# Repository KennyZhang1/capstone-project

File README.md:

# Introduction
This repo contains the source code for our ECE Capstone Project: Robotic Vehicle Glove Controller

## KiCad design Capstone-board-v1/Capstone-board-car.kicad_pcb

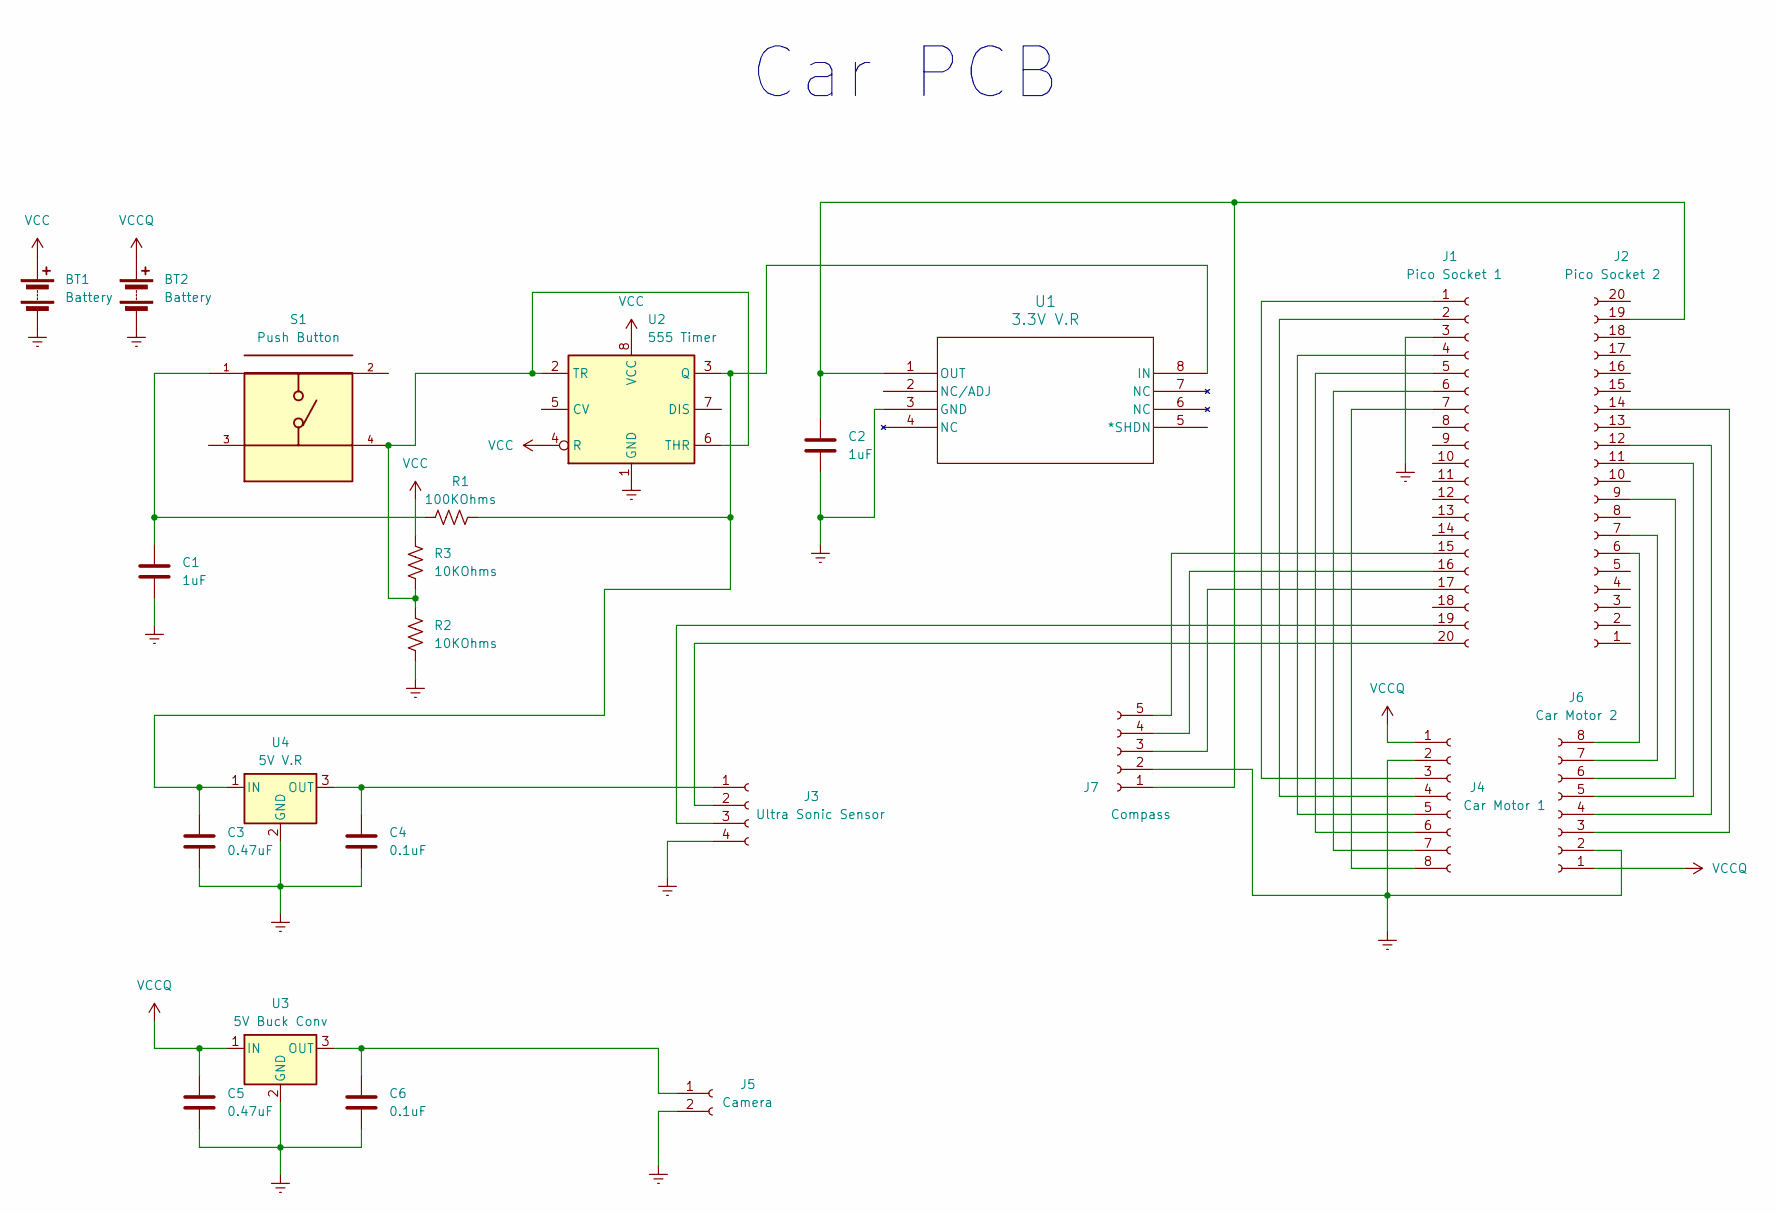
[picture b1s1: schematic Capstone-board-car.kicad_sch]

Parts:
BT1: Battery; Hirose_DF11-6DP-2DSA_2x03_P2.00mm_Vertical
BT2: Battery; PinHeader_1x02_P2.54mm_Vertical
C1, C2: 1uF; CP_Radial_Tantal_D4.5mm_P5.00mm
C3, C5: 0.47uF; CP_Radial_Tantal_D4.5mm_P5.00mm
C4, C6: 0.1uF; CP_Radial_Tantal_D4.5mm_P5.00mm
J1: Pico Socket 1; PinSocket_1x20_P2.54mm_Vertical
J2: Pico Socket 2; PinSocket_1x20_P2.54mm_Vertical
J3: Ultra Sonic Sensor; PinHeader_1x04_P2.54mm_Vertical
J4: Car Motor 1; PinHeader_1x08_P2.54mm_Vertical
J5: Camera; PinHeader_1x02_P2.54mm_Vertical
J6: Car Motor 2; PinSocket_1x08_P2.54mm_Vertical
J7: Compass; PinSocket_1x05_P2.54mm_Vertical
R1: 100KOhms; R_Axial_DIN0204_L3.6mm_D1.6mm_P5.08mm_Horizontal
R2, R3: 10KOhms; R_Axial_DIN0204_L3.6mm_D1.6mm_P5.08mm_Horizontal
S1: Push Button; SW_TS02-66-60-BK-160-LCR-D; PARTREV 1.0
U1: 3.3V V.R; DIP-8_W7.62mm_Socket
U2: 555 Timer; DIP-8_W7.62mm_Socket
U3: 5V Buck Conv; TO255P1040X460X1968-3
U4: 5V V.R; TO255P1040X460X1968-3

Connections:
Earth: BT1.2 (-), BT2.2 (-), C1.2, C2.2, C3.2, C4.2, C5.2, C6.2, J1.3, J3.4, J4.2, J5.2, J6.2, J7.2, R2.1, U1.3 (GND), U2.1 (GND), U3.2 (GND), U4.2 (GND)
unnamed: C1.1, R1.1, S1.1
unnamed: J1.1, J4.3
unnamed: J1.2, J4.4
unnamed: J1.4, J4.5
unnamed: J1.5, J4.6
unnamed: J1.6, J4.7
unnamed: J1.7, J4.8
unnamed: J1.15, J7.5
unnamed: J1.16, J7.4
unnamed: J1.17, J7.3
unnamed: J1.19, J3.3
unnamed: J1.20, J3.2
unnamed: J2.6, J6.8
unnamed: J2.7, J6.7
unnamed: J2.9, J6.6
unnamed: J2.11, J6.5
unnamed: J2.12, J6.4
unnamed: J2.14, J6.3
unnamed: C2.1, J2.19, J7.1, U1.1 (OUT)
unnamed: C4.1, J3.1, U4.3 (OUT)
unnamed: C6.1, J5.1, U3.3 (OUT)
unnamed: C3.1, R1.2, U1.8 (IN), U2.3 (Q), U4.1 (IN)
unnamed: R2.2, R3.1, S1.4, U2.2 (TR), U2.6 (THR)
VCC: BT1.1 (+), R3.2, U2.4 (R), U2.8 (VCC)
VCCQ: BT2.1 (+), C5.1, J4.1, J6.1, U3.1 (IN)

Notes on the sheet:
Car PCB

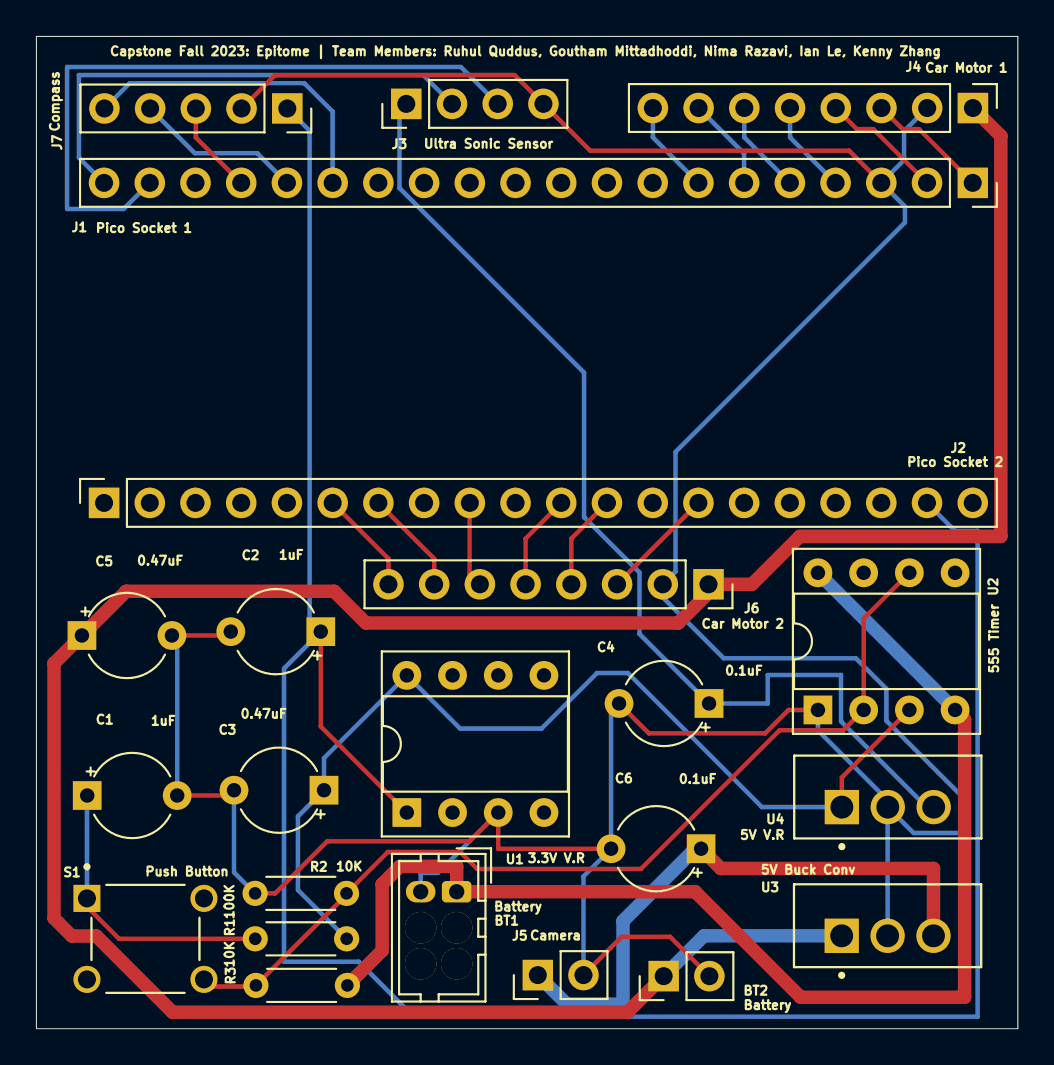
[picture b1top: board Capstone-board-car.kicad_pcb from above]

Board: 2 copper layers, 54.5 x 55.1 mm, 23 parts (0 on the bottom side), 26 nets.

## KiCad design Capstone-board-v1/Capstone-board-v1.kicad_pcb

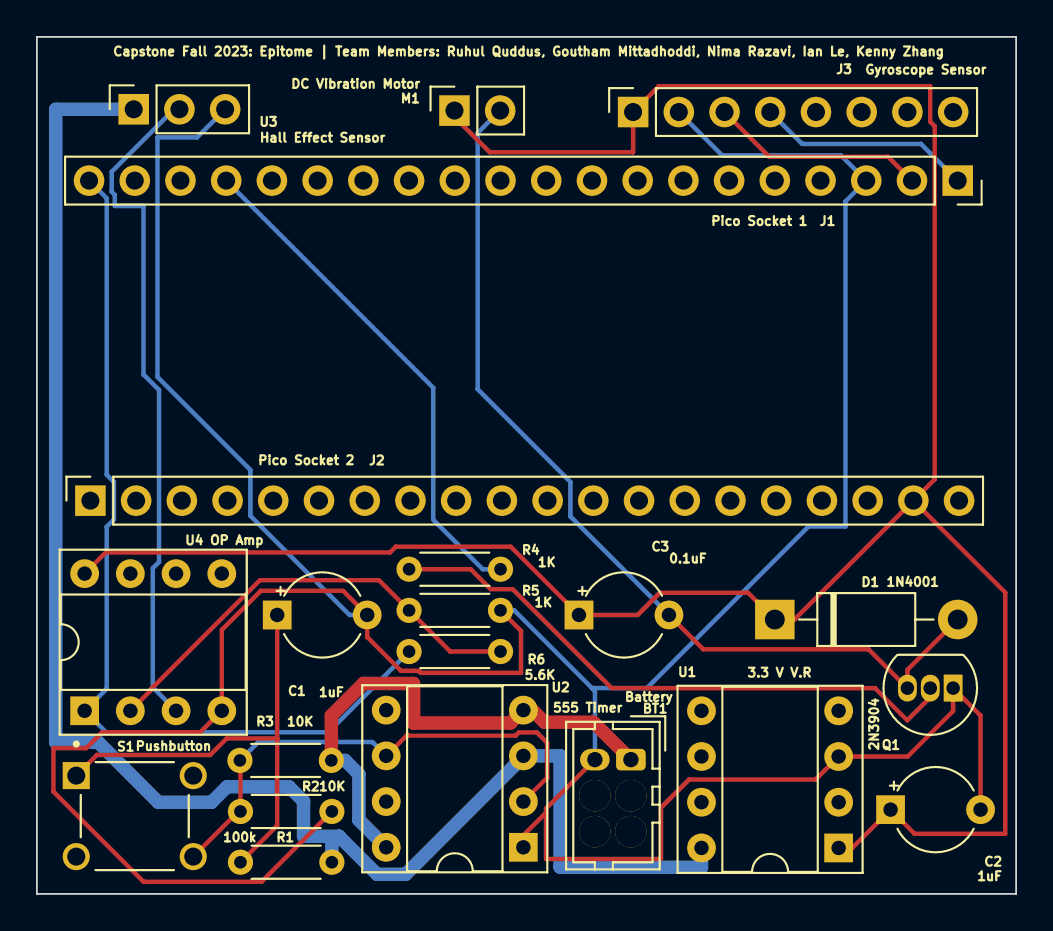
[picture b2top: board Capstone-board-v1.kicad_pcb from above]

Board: 2 copper layers, 54.4 x 47.6 mm, 21 parts (0 on the bottom side), 14 nets.

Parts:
BT1: Battery; Hirose_DF11-6DP-2DSA_2x03_P2.00mm_Vertical
C1, C2: 1uF; CP_Radial_Tantal_D4.5mm_P5.00mm
C3: 0.1uF; CP_Radial_Tantal_D4.5mm_P5.00mm
D1: 1N4001; D_DO-41_SOD81_P10.16mm_Horizontal
J1: Pico Socket 1; PinSocket_1x20_P2.54mm_Vertical
J2: Pico Socket 2; PinSocket_1x20_P2.54mm_Vertical
J3: Gyroscope Sensor; PinSocket_1x08_P2.54mm_Vertical
M1: DC Vibration Motor; PinSocket_1x02_P2.54mm_Vertical
Q1: 2N3904; TO-92_Inline
R1: 100k; R_Axial_DIN0204_L3.6mm_D1.6mm_P5.08mm_Horizontal
R2, R3: 10K; R_Axial_DIN0204_L3.6mm_D1.6mm_P5.08mm_Horizontal
R4, R5: 1K; R_Axial_DIN0204_L3.6mm_D1.6mm_P5.08mm_Horizontal
R6: 5.6K; R_Axial_DIN0204_L3.6mm_D1.6mm_P5.08mm_Horizontal
S1: Pushbutton; SW_TS02-66-60-BK-160-LCR-D
U1: 3.3 V V.R; DIP-8_W7.62mm_Socket
U2: 555 Timer; DIP-8_W7.62mm_Socket
U3: Hall Effect Sensor; PinSocket_1x03_P2.54mm_Vertical
U4: OP Amp; DIP-8_W7.62mm_Socket

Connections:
Earth: BT1.2 (-), C1.2, C2.2, J1.3, J3.2, Q1.1 (E), R2.1, R5.2, U1.3 (GND), U2.1 (GND), U3.3 (GND), U4.4 (V-)
unnamed: C1.1, R1.1, S1.1
unnamed: C3.2, D1.2 (A), M1.2 (-), Q1.3 (C)
unnamed: C2.1, C3.1, D1.1 (K), J2.19, J3.1, M1.1 (+), U1.1 (OUT), U4.8 (V+)
unnamed: J1.1, J3.4
unnamed: J1.2, J3.3
unnamed: J1.17, R4.2
unnamed: J1.20, R6.1, U4.1
unnamed: Q1.2 (B), R4.1
unnamed: R1.2, U1.8 (IN), U2.3 (Q), U3.1 (VCC)
unnamed: R2.2, R3.1, S1.4, U2.2 (TR), U2.6 (THR)
unnamed: U3.2 (VOUT), U4.3 (+)
unnamed: R5.1, R6.2, U4.2 (-)
VCC: BT1.1 (+), R3.2, U2.4 (R), U2.8 (VCC)

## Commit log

2023-08-28 added source
2023-09-02 Committing initial gyro and ultrasonic tests
2023-09-08 added constants
2023-09-15 Added pico client code
2023-09-22 code to send gyro data and recv ultrasonic data
2023-09-22 added cleanup code
2023-09-22 changes to picoserver to send usonic data back by tcp, some motor test code
2023-09-23 bluetooth client for pico to pico cross comms
2023-09-23 server for bluetooth pico to pico cross comms
2023-09-27 Counter send and receive tests
2023-10-07 Footprints and libraries
2023-10-07 How to import
2023-10-09 moving car code to git, includes all the bluetooth additions
2023-10-09 Updating glove code, including bluetooth stuff
2023-10-10 correct footprints
2023-10-11 so far
2023-10-12 schematic
2023-10-12 ready for tracing
2023-10-12 correct hole size
2023-10-17 traces added
2023-10-17 All routing done.
2023-10-18 Some footprints fixed.
2023-10-18 Final traces done
2023-10-18 reference designators added
2023-10-20 Final PCB completed!
2023-10-24 Final PCB's done.
2023-11-08 STABLE VERSION: Demo glove code
    Code will be modified for speed ramping soon
2023-11-08 Car code with backtrack
2023-11-10 New Car Code Changes
2023-11-10 solved merge conflicts
2023-11-11 Car Code Clean up
2023-11-11 continuous orientation lock mode
    does not include support for spin turns
    does not ramp power
    does not correct drift
2023-11-13 Final PCBs done!
2023-11-14 first
2023-11-26 Push for pending changes
2023-11-27 IN PROGRESS drift correct with compass,
2023-11-27 more glove box
2023-12-01 Finished backtracking/disconnect code
